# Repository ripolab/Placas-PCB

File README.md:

# Placas-PCB
Diseño de placas PCB

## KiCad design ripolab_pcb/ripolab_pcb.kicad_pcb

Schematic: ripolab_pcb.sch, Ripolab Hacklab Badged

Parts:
C1, C4: 47uF; C_0805_2012Metric_Pad1.15x1.50mm_HandSolder
C2: 100nF; C_0805_2012Metric_Pad1.15x1.50mm_HandSolder
C3: 10nF; C_0805_2012Metric_Pad1.15x1.50mm_HandSolder
D1: D_Schottky_ALT; D_SOD-123
GND_1: GND; TestPad
J1: Conn_01x02; Molex_PicoBlade_53261-0271_1x02_P1.25mm_Horizontal
LED1, LED2, LED3, LED4, LED5, LED6, LED7, LED8: WS2812B; LED_WS2812B-PLCC4
ON1: LED; LED_0805_2012Metric
PROG1: SW_Push; SW_SPST_TL3342
R1, R2, R3, R4, R5: 10K; R_0805_2012Metric
R6: 1K; R_0805_2012Metric
R7: 10K; R_0805_2012Metric_Pad1.15x1.50mm_HandSolder
RST1: SW_Push RESET; SW_SPST_TL3342
RST_1: TEST_1P; TestPad
RX_1: RX; TestPad
SW1: SPDT; SW_SPDT_PCM12
TX_1: TX; TestPad
U1: ESP-12E; ESP-12E_SMD
U2: SPX3819M5-L-3-3; SOT-23-5
VCC_1: TEST_VCC; TestPad

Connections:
+3,3V: C1.2, C3.1, C4.1, LED1.3, LED2.3, LED3.3, LED4.3, LED5.3, LED6.3, LED7.3, LED8.3, R1.1, R2.1, R4.1, R5.1, R6.1, U1.8, U2.5 (OUT), VCC_1.1
CH_PD: R1.2, U1.3
GND: C1.1, C2.2, C3.2, C4.2, GND_1.1, J1.2, LED1.1, LED2.1, LED3.1, LED4.1, LED5.1, LED6.1, LED7.1, LED8.1, ON1.1, PROG1.1, R3.1, RST1.1, U1.15, U2.2 (GND)
GPIO0: PROG1.2, R2.2, U1.18
GPIO2: R5.2, U1.17
GPIO4: LED1.2, U1.19
GPIO15: R3.2, U1.16
unnamed: C2.1, D1.1, R7.1, U2.1 (IN)
unnamed: LED1.4, LED2.2
unnamed: LED2.4, LED3.2
unnamed: LED3.4, LED4.2
unnamed: LED4.4, LED5.2
unnamed: LED5.4, LED6.2
unnamed: LED6.4, LED7.2
unnamed: LED7.4, LED8.2
unnamed: ON1.2, R6.2
unnamed: R7.2, U2.3 (EN)
Reset: R4.2, RST1.2, RST_1.1, U1.1
Rx: RX_1.1, U1.21
Tx: TX_1.1, U1.22
VBAT: J1.1, SW1.2
VBAT_SW: D1.2, SW1.1

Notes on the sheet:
Módulo ESP8266
Neopixels WS2812B
Alimentación
Configuracion + Push B

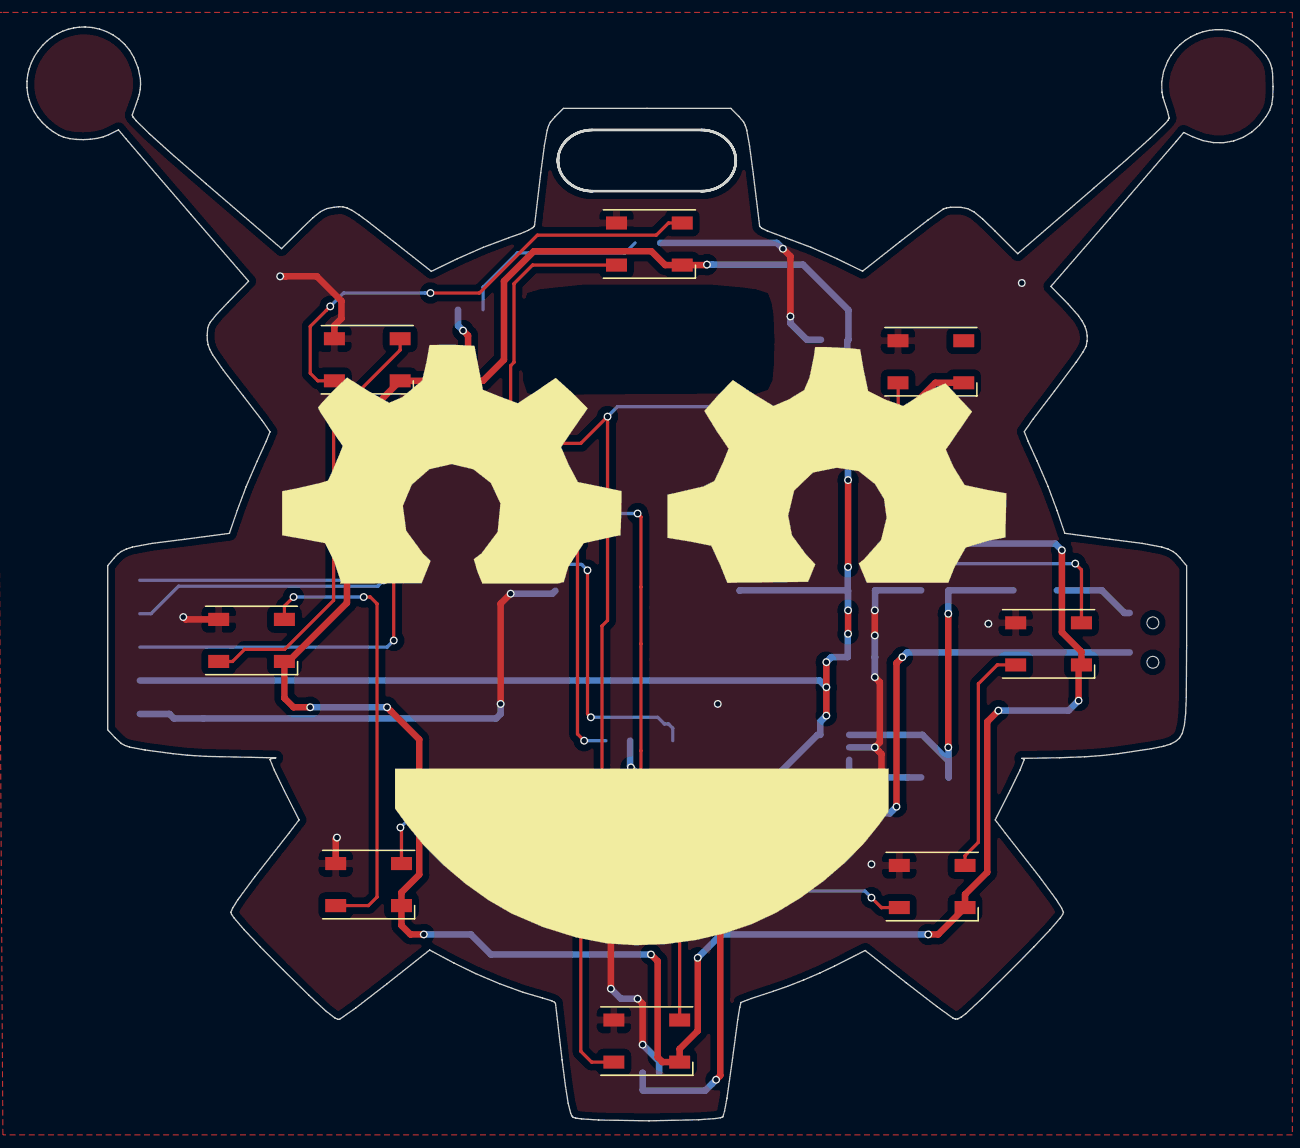
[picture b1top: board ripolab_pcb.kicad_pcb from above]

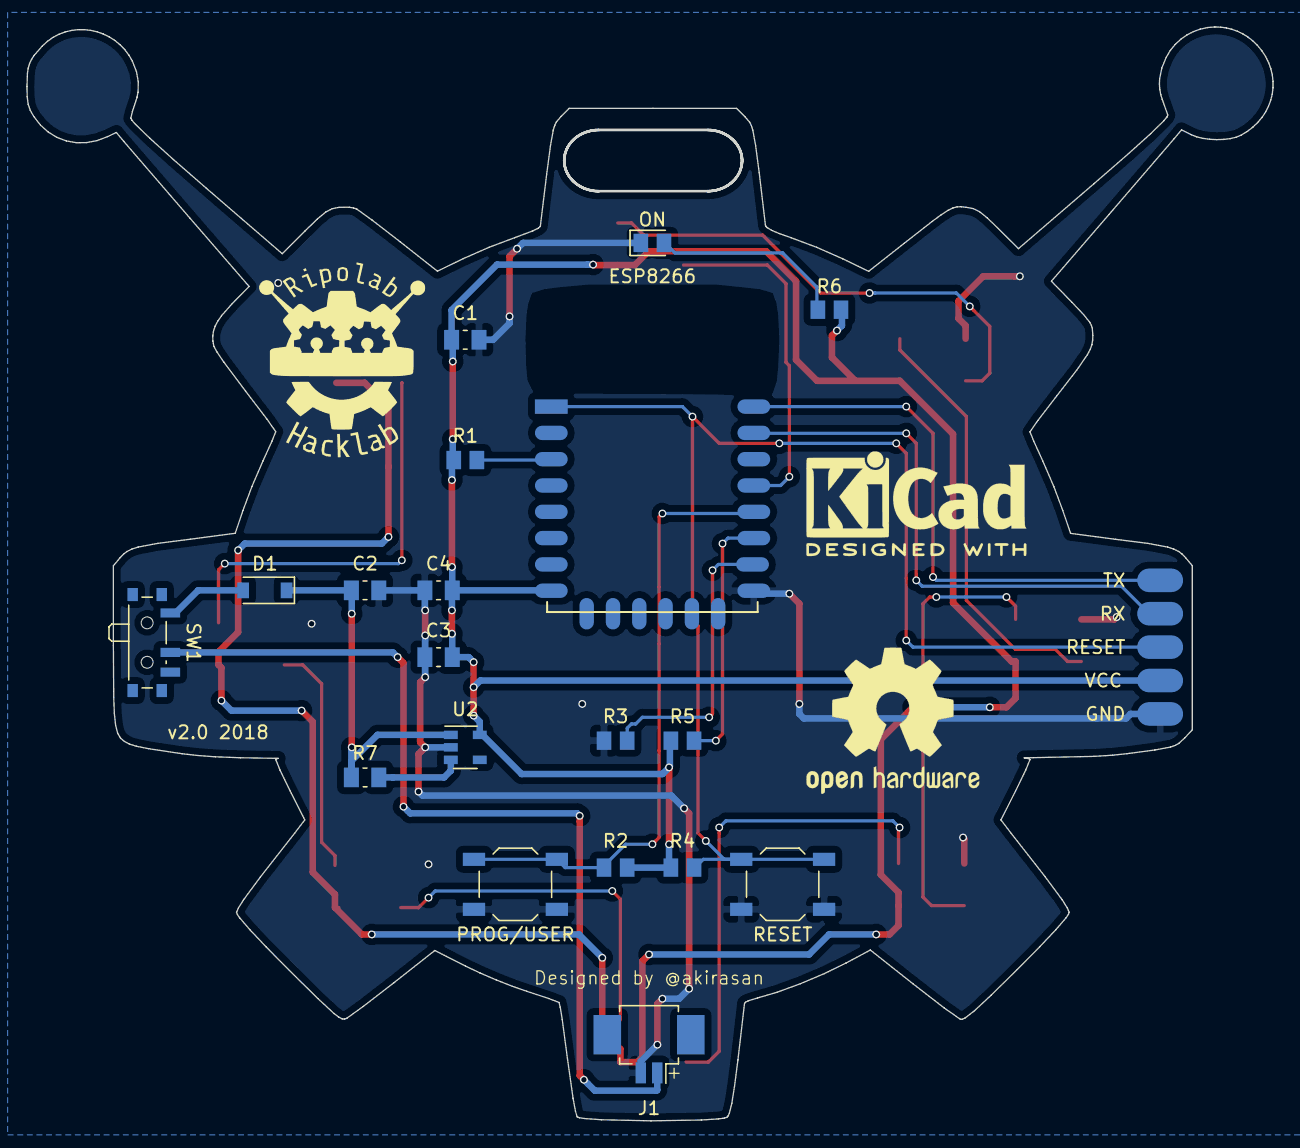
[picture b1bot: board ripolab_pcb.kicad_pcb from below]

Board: 2 copper layers, 94.6 x 83.1 mm, 34 parts (25 on the bottom side), 22 nets.

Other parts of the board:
svg2mod: G***; logo_pcb_cara.pretty
svg2mod#2: G***; logo_ripolab_12x14mm

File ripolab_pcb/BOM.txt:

Comp            Cantidad    Nombre
U1                  1       ESP8266-12                          https://es.aliexpress.com/item/ESP8266-12-F-Remote-Serial-Po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
J1                  1       Molex Pico-blade 1.25mm             https://es.aliexpress.com/item/50sets-JST-Molex-1-25mm-Pitch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
SW1                 1                                           https://es.aliexpress.com/item/50-unids-mini-7-Pasadores-enc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
D1                  1       Diodo Schottky                      https://es.aliexpress.com/item/Xin-Yang-electr-nico-env-o-li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
C2                  1       100nF                               https://es.aliexpress.com/item/500pcs-100nF-X7R-Error-10-50V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
R1,R2,R3,R4,R5,R7   6       10K                                 https://es.aliexpress.com/item/SMD-Resistance-0805-10K-1-1-8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
U2                  1       Regulador 3.3V SPX3819M5-L-3-3      https://es.aliexpress.com/item/10PCS-SPX3819-3-3-SPX3819M5-L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
C3                  1       10nF                                https://es.aliexpress.com/item/Free-shipping-0805-SMD-capaci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
C4,C1               2       47uF                                https://es.aliexpress.com/item/Free-shipping-0805-SMD-capaci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
WS2812B             8       WS2812B                             https://es.aliexpress.com/item/WS2812B-LED-Chip-10-1000pcs-5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
R6                  1       1K                                  https://es.aliexpress.com/item/SMD-Resistance-0805-1K-1-K-oh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
LED_ON1             1       LED SMD                             https://es.aliexpress.com/item/100-unids-LED-SMD-0805-2012-c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
RST,PROG            2                                           https://es.aliexpress.com/item/100PC-Lot-SMD-4-4-1-5MM-4X4X1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

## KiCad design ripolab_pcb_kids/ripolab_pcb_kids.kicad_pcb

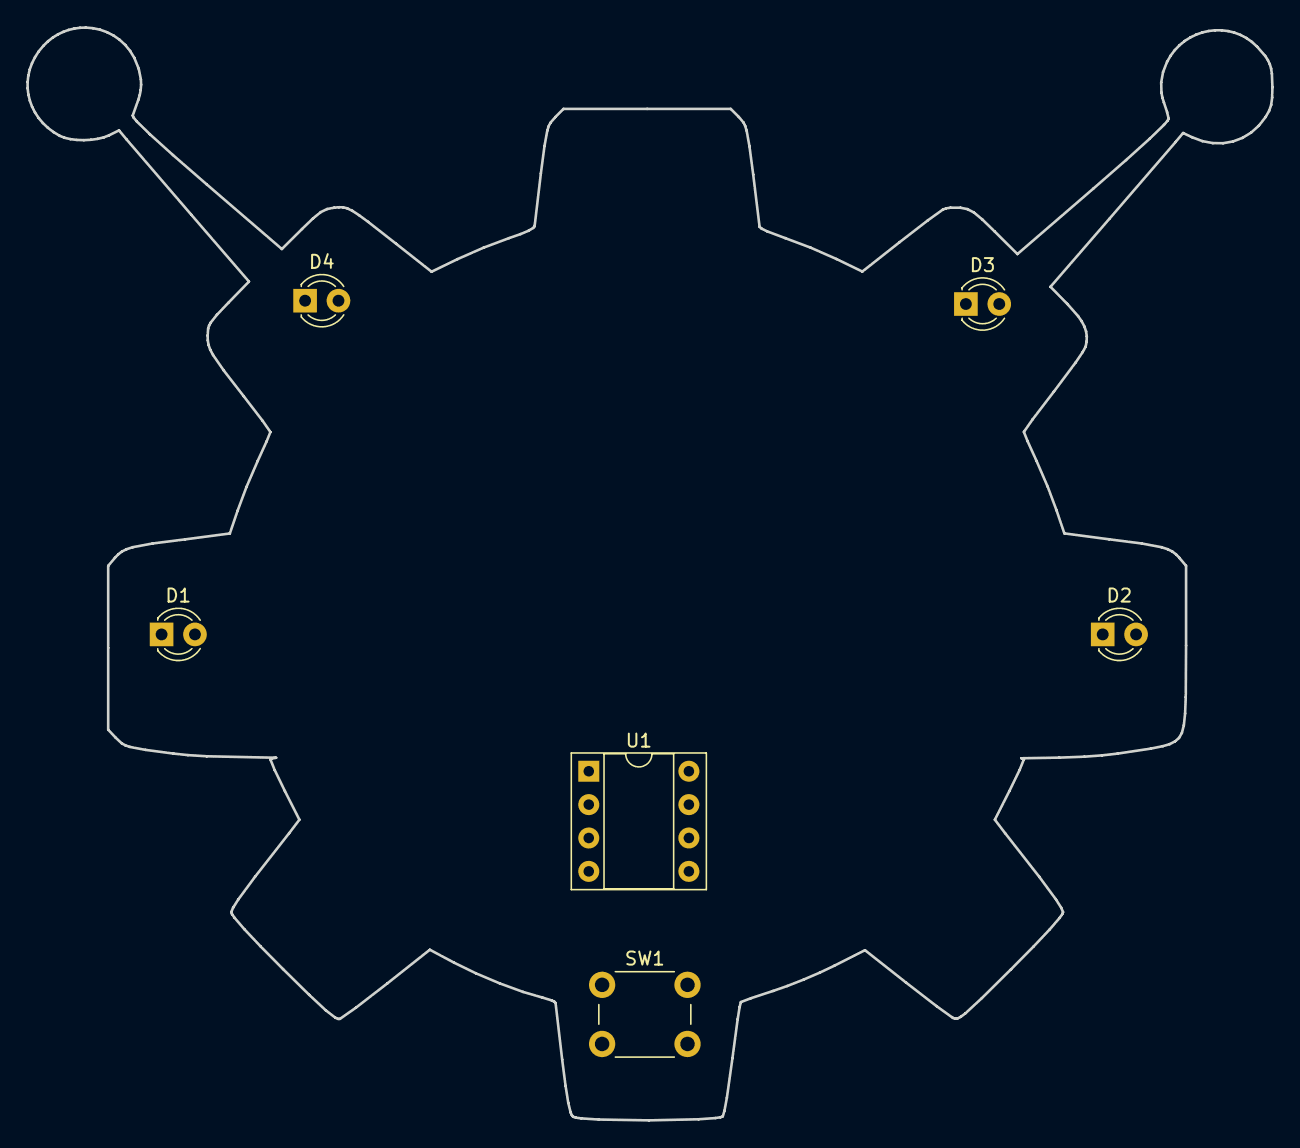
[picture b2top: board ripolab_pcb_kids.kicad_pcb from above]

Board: 2 copper layers, 94.7 x 83.2 mm, 6 parts (0 on the bottom side), 6 nets, no tracks yet.

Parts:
D1, D2, D3, D4: LED; LED_D3.0mm
SW1: SW_DIP_x02; SW_PUSH_6mm
U1: LM555; DIP-8_W7.62mm_Socket

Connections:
GND: D1.1, U1.1
unnamed: D1.2, D2.1
unnamed: D2.2, D3.1
unnamed: D3.2, D4.1
unnamed: D4.2, U1.5
unnamed: SW1.2, U1.8

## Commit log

2018-02-21 Primera aportacion
2018-04-04 badge ripolab v1
2018-05-01 version 2.0 (corrección v1.0)
2018-05-23 v2 update + BOM
2018-08-13 PCB Saba-TIC 2018
    PCB de la badge de Saba-TIC 2018 para el taller de soldadura familiar
2018-09-09 Actualización final tras taller
    Actualización final tras el taller, incluyendo documentación y piezas 3D utilizadas para la mesa de trabajo.
2019-04-06 RoboTAC 2019
